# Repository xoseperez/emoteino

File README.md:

# Moteino Energy Monitor

A simple energy monitor shield for Moteino and the needed firmware to make it work with different configurations.

## Features

* LiPo battery connector with battery monitor at A7 (470k resistors for low power)
* Simple biased reading (low consumption voltage divider) with optional burden resistor
* 3.5mm jack input compatible with most CT out there
* Stackable up to 3 shields to read 3 different lines.
* Jumper pads to select input pin (A1, A2 or A3)

Check my **[Moteino Energy Monitor Shield][1]** post for further information about this project.

## Hardware

The hardware is shield for **Moteino** with a **battery monitor circuitry** and a **3.5mm plug** for commonly available current transformers (a.k.a. non-invasive current sensors). There is a footprint for an optional burden resistor (SMD0805) and a bias voltage divider using 2 470K resistors for low power consumption.

The battery monitoring is based on a voltage divider with (again) two 470k resistors. The downstream resistor is tied to GND and the mid point to A7.

## Firmware for Moteino + RFM69

### Dependencies

The code is very straight forward and there are comments where I thought it was important. It uses the following libraries:

* **[RFM69_ATC][3]** by Felix Rusu and Thomas Studwell
* **[Low-Power][4]** by RocketScream

These libraries will be automatically installed if you use [PlatformIO][2].

It also relies on my **RFM69Manager library** to wrap RFM69_ATC. This library manages radio setup and also message sending protocol. Messages from this node have the following format: ```<key>:<value>:<packetID>```. Packet ID is then used in the gateway to detect duplicates or missing packets from a node. If you don't want to send the packetID change the SEND_PACKET_ID value in RFM69Manager.h to 0.

### Configuration

Rename or copy the settings.h.sample file to settings.h and change its values to fit your needs. Check the descriptions for each value.

### Flashing

The project is ready to be build using **[PlatformIO][2]**.
Please refer to their web page for instructions on how to install the builder. Once installed connect the Moteino to your favourite FTDI-like programmer and:

```bash
> platformio run --target upload
```

[1]: http://tinkerman.cat/moteino-energy-monitor-shield/
[2]: http://www.platformio.org
[3]: https://github.com/LowPowerLab/RFM69
[4]: https://github.com/rocketscream/Low-Power/

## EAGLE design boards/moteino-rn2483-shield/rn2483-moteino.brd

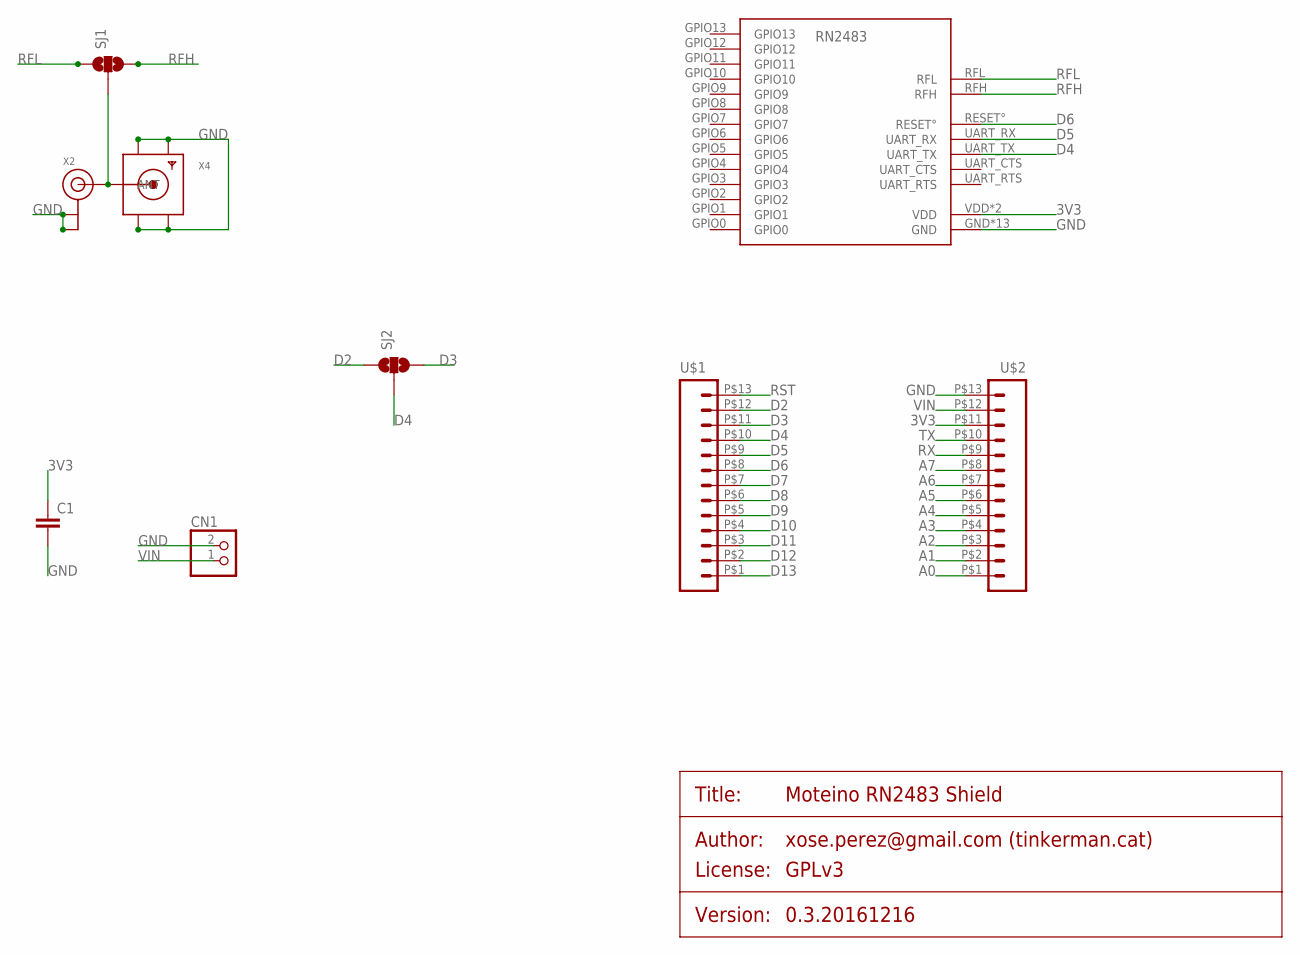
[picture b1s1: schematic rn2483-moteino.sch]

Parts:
C1: C-EU0805; 0805
CN1: JST_2PIN-SMT-RA; JST-PH-2-SMT-RA
RN2483: RN2483ALLPINS; RN2483
SJ1, SJ2: SOLDERJUMPER_2WAYS; SJ_3
U$1, U$2: M13M13_1X13_SMD; 1X13_SMD
X2: ANTENNA_U.FL; U.FL
X4: SMACONNECTOR_EDGE; SMA_EDGELAUNCH

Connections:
3V3: C1.1, RN2483.VDD, RN2483.VDD2 (VDD), U$2.P$11 (11)
A0: U$2.P$1 (1)
A1: U$2.P$2 (2)
A2: U$2.P$3 (3)
A3: U$2.P$4 (4)
A4: U$2.P$5 (5)
A5: U$2.P$6 (6)
A6: U$2.P$7 (7)
A7: U$2.P$8 (8)
D2: SJ2.1, U$1.P$12 (12)
D3: SJ2.3, U$1.P$11 (11)
D4: RN2483.UART_TX, SJ2.2, U$1.P$10 (10)
D5: RN2483.UART_RX, U$1.P$9 (9)
D6: RN2483.RESET°, U$1.P$8 (8)
D7: U$1.P$7 (7)
D8: U$1.P$6 (6)
D9: U$1.P$5 (5)
D10: U$1.P$4 (4)
D11: U$1.P$3 (3)
D12: U$1.P$2 (2)
D13: U$1.P$1 (1)
GND: C1.2, CN1.2 (1), RN2483.GND, RN2483.GND1 (GND), RN2483.GND2 (GND), RN2483.GND3 (GND), RN2483.GND4 (GND), RN2483.GND5 (GND), RN2483.GND6 (GND), RN2483.GND7 (GND), RN2483.GND8 (GND), RN2483.GND9 (GND), RN2483.GND10 (GND), RN2483.GND11 (GND), RN2483.GND12 (GND), U$2.P$13 (13), X2.1 (GND), X2.2 (GND), X4.GND@1 (GND4), X4.GND@2 (GND3), X4.GND@3 (GND2), X4.GND@4 (GND1)
unnamed: SJ1.2, X2.3 (SIGNAL), X4.P (ANT)
RFH: RN2483.RFH, SJ1.3
RFL: RN2483.RFL, SJ1.1
RST: U$1.P$13 (13)
RX: U$2.P$9 (9)
TX: U$2.P$10 (10)
VIN: CN1.1 (2), U$2.P$12 (12)

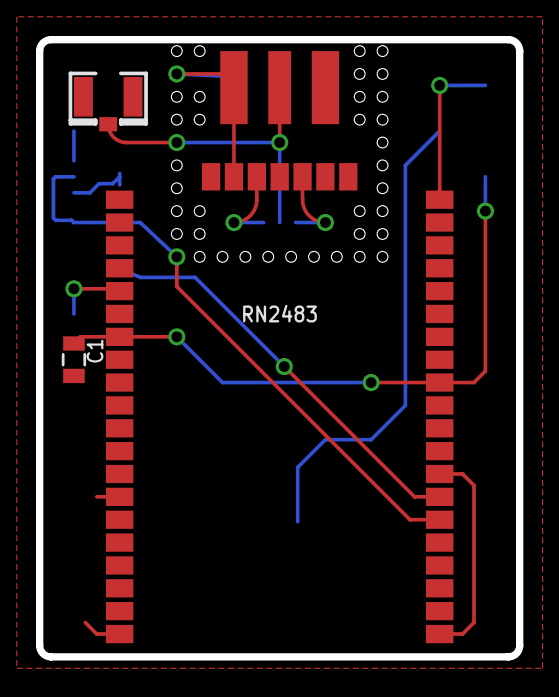
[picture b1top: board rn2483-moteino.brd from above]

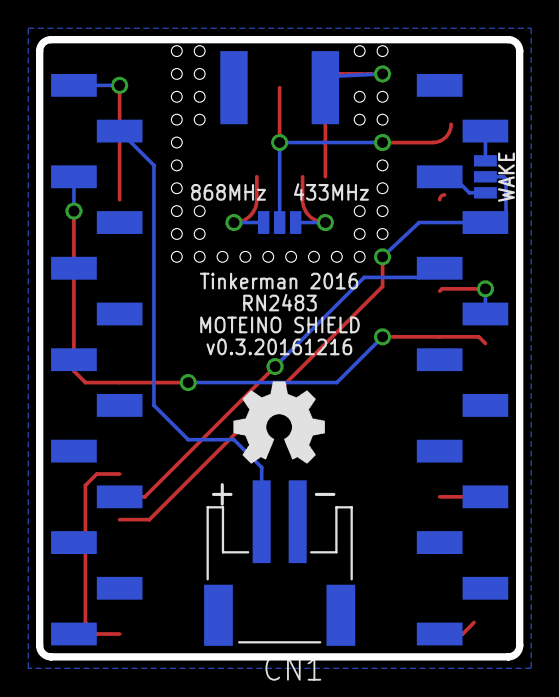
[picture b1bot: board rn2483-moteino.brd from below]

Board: 2 copper layers, 26.7 x 34.3 mm, 9 parts (5 on the bottom side), 11 nets.

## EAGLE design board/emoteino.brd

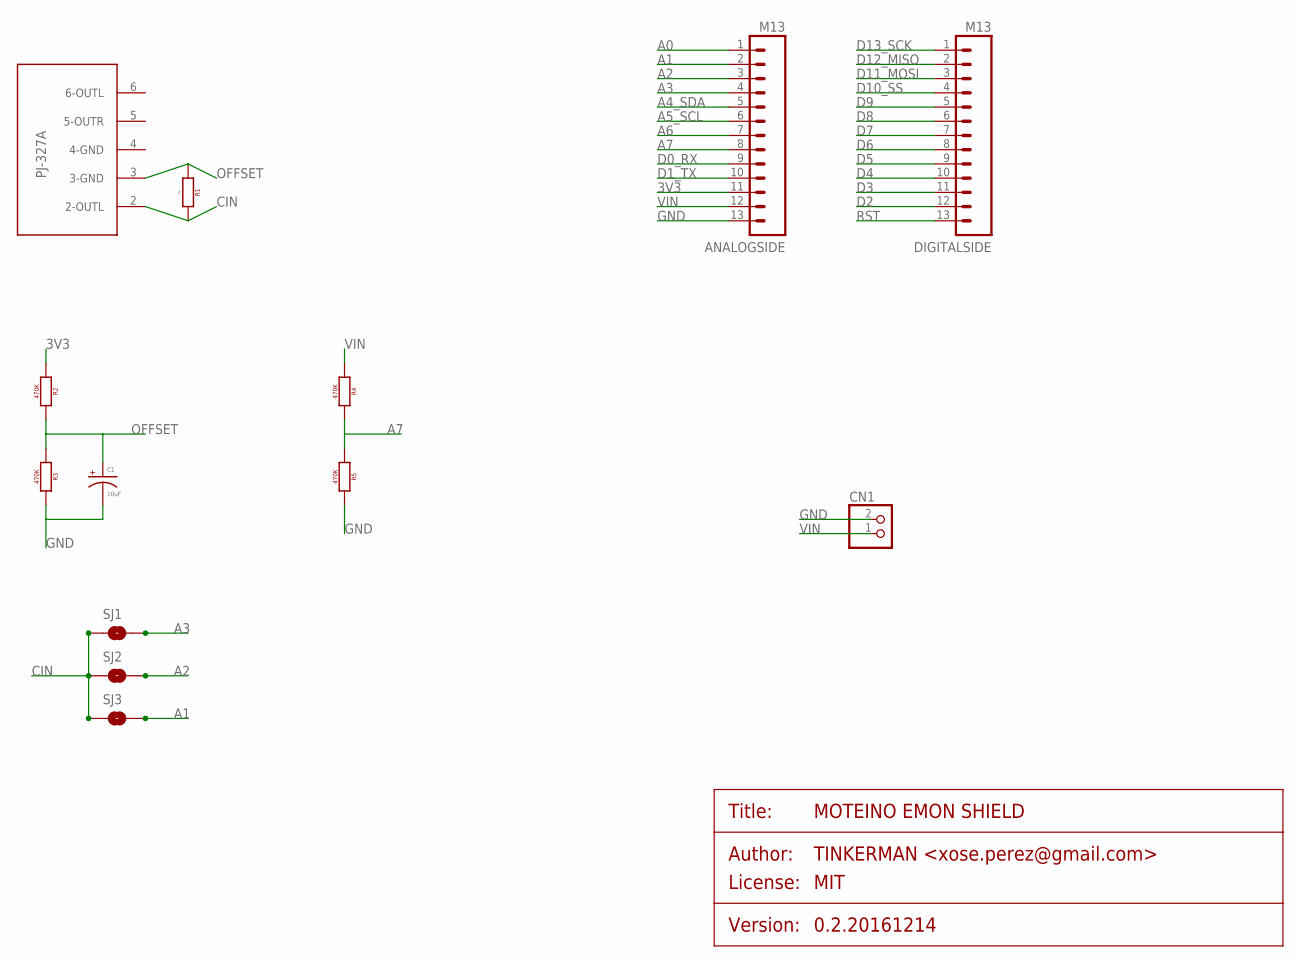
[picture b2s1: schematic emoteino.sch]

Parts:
ANALOGSIDE: M13; 1X13_NO_SILK
C1: 10uF; CPOL-RADIAL-10UF-25V
CN1: JST_2PIN-SMT-RA; JST-PH-2-SMT-RA
CURR1: PJ-327A
DIGITALSIDE: M13; 1X13_NO_SILK
R1: 0805
R2, R3, R4, R5: 470K; 0805
SJ1, SJ2, SJ3: SOLDERJUMPERNO; SJ_2S-NO

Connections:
3V3: ANALOGSIDE.11, R2.1
A0: ANALOGSIDE.1
A1: ANALOGSIDE.2, SJ3.2
A2: ANALOGSIDE.3, SJ2.2
A3: ANALOGSIDE.4, SJ1.2
A4_SDA: ANALOGSIDE.5
A5_SCL: ANALOGSIDE.6
A6: ANALOGSIDE.7
A7: ANALOGSIDE.8, R4.2, R5.1
CIN: CURR1.2 (2-OUTL), R1.2, SJ1.1, SJ2.1, SJ3.1
D0_RX: ANALOGSIDE.9
D1_TX: ANALOGSIDE.10
D2: DIGITALSIDE.12
D3: DIGITALSIDE.11
D4: DIGITALSIDE.10
D5: DIGITALSIDE.9
D6: DIGITALSIDE.8
D7: DIGITALSIDE.7
D8: DIGITALSIDE.6
D9: DIGITALSIDE.5
D10_SS: DIGITALSIDE.4
D11_MOSI: DIGITALSIDE.3
D12_MISO: DIGITALSIDE.2
D13_SCK: DIGITALSIDE.1
GND: ANALOGSIDE.13, C1.2 (-), CN1.2 (1), R3.2, R5.2
OFFSET: C1.1 (+), CURR1.3 (3-GND), R1.1, R2.2, R3.1
RST: DIGITALSIDE.13
VIN: ANALOGSIDE.12, CN1.1 (2), R4.1

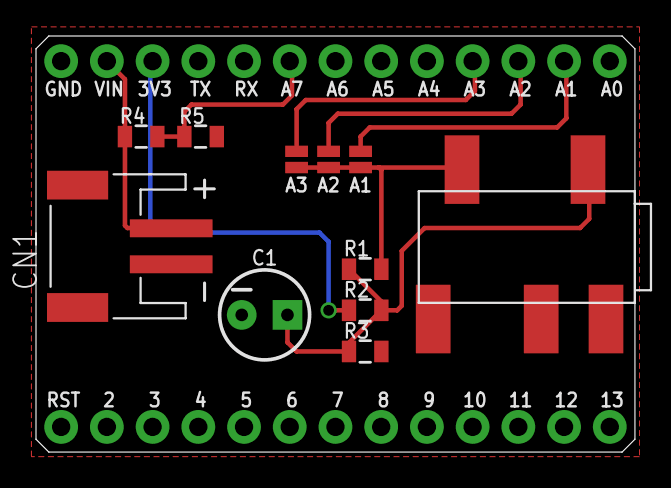
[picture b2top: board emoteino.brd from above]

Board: 2 copper layers, 33.3 x 23.1 mm, 13 parts (0 on the bottom side), 9 nets.

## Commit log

2016-12-16 Clean up Moteino Energy Monitor Shield board
2016-12-16 Moteino RN2483 Shield
2016-12-16 Moteino LoRaWan Energy Monitor code based on RN2483. Initial commit
2018-01-24 Changes in the schematic
2018-01-24 Using a local copy of TTN library
2018-01-24 RFM95 examples for Moteino, Wemos Lora Shield and ESP32
2021-05-07 Disable ATC, sending MAX power consumption

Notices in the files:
board/emoteino.sch:
PROJECT_LICENSE: MIT
boards/moteino-rn2483-shield/rn2483-moteino.sch:
PROJECT_LICENSE: GPLv3
